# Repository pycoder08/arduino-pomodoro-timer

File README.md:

# Arduino Pomodoro Timer

A desktop focus timer I built around an Arduino Mega, a 16x2 LCD, three push buttons, a buzzer, and an RGB LED. It runs configurable focus/break cycles and signals each transition with color and sound.

## Status

The breadboard prototype works — I've run the timer through its focus and break cycles on it. The schematic and PCB layout are drawn in KiCad and included here. I'm currently soldering the circuit onto an Arduino protoshield.

I have not fabricated the custom PCB yet, so the layout is a work in progress rather than something I'd send to a fab house today. Routing and design-rule checks still need a pass.

## Features

- Three focus/break presets: 25/5, 15/5, and 50/10 minutes
- Start, pause, and resume, with the remaining time preserved across a pause
- Tap Reset to skip to the next phase; hold it for a second to cancel the session outright
- Preset selection with the mode button while idle, remembered in EEPROM across power cycles
- Count of sessions finished since power-on, shown on the idle screen
- Countdown on a 16x2 LCD
- Red RGB LED breathing during focus, solid green during breaks
- Multi-note buzzer melodies at session transitions

Button handling, the melodies, and the LED breathing are all non-blocking, so the countdown
stays accurate and the buttons stay responsive no matter what else is happening.

## Hardware

Arduino Mega 2560, 16x2 LCD, three push buttons, a passive buzzer, a common-cathode RGB LED,
resistors, breadboard, and jumper wire. LCD contrast comes from a fixed divider (roughly 8.5k to
5V and 1k to ground) rather than a trim potentiometer, so no pin is spent on it.

The sketch drives the RGB LED on pins 44–46. Those are PWM-capable on the Mega, which the
breathing effect needs, and they don't exist on a Uno — remap them if you build this on a smaller
board. I still need to document exact component models and resistor values.

### Pin assignments

| Function | Arduino pin |
| --- | --- |
| LCD RS | 12 |
| LCD enable | 11 |
| LCD D4–D7 | 5, 4, 3, 2 |
| Start / pause | 6 |
| Reset | 7 |
| Mode | 8 |
| Buzzer | 9 |
| RGB red | 44 |
| RGB blue | 45 |
| RGB green | 46 |

Buttons are wired active-low using `INPUT_PULLUP` and are debounced in software. This table covers
the software pin assignment only — check LCD contrast wiring, your RGB LED's common pin, and
current-limiting resistors against your own build.

## Running it

1. Open `timer.ino` in the Arduino IDE, letting it create the enclosing `timer` folder if prompted.
2. Make sure the `LiquidCrystal` library is installed. `EEPROM` ships with the IDE.
3. Select your board and port, confirming the pins above exist on it.
4. Compile and upload.

## KiCad files

`Timer.kicad_pro` is the main project, with `Timer.kicad_sch` for the schematic and `Timer.kicad_pcb` for the layout. `Arduino_MountingHole.pretty` holds the custom mounting-hole footprints the board references.

`focus_timer_schematic.kicad_sch` is an earlier sheet covering just the Arduino header connections, kept for reference.

## A note on the code

I wrote this project's firmware with AI assistance. The circuit design, breadboard build and testing, schematic capture, PCB layout, and protoshield assembly are my own work.

## To do

- Finish the protoshield soldering and retest every control
- Document component models and resistor values
- Run design-rule checks on the PCB before fabricating
- Test all three presets, pause/resume in both phases, tap and hold Reset, and the full
  focus-to-break transition
- Persist the session count across power cycles, or roll it over on a real clock rather than at
  power-on

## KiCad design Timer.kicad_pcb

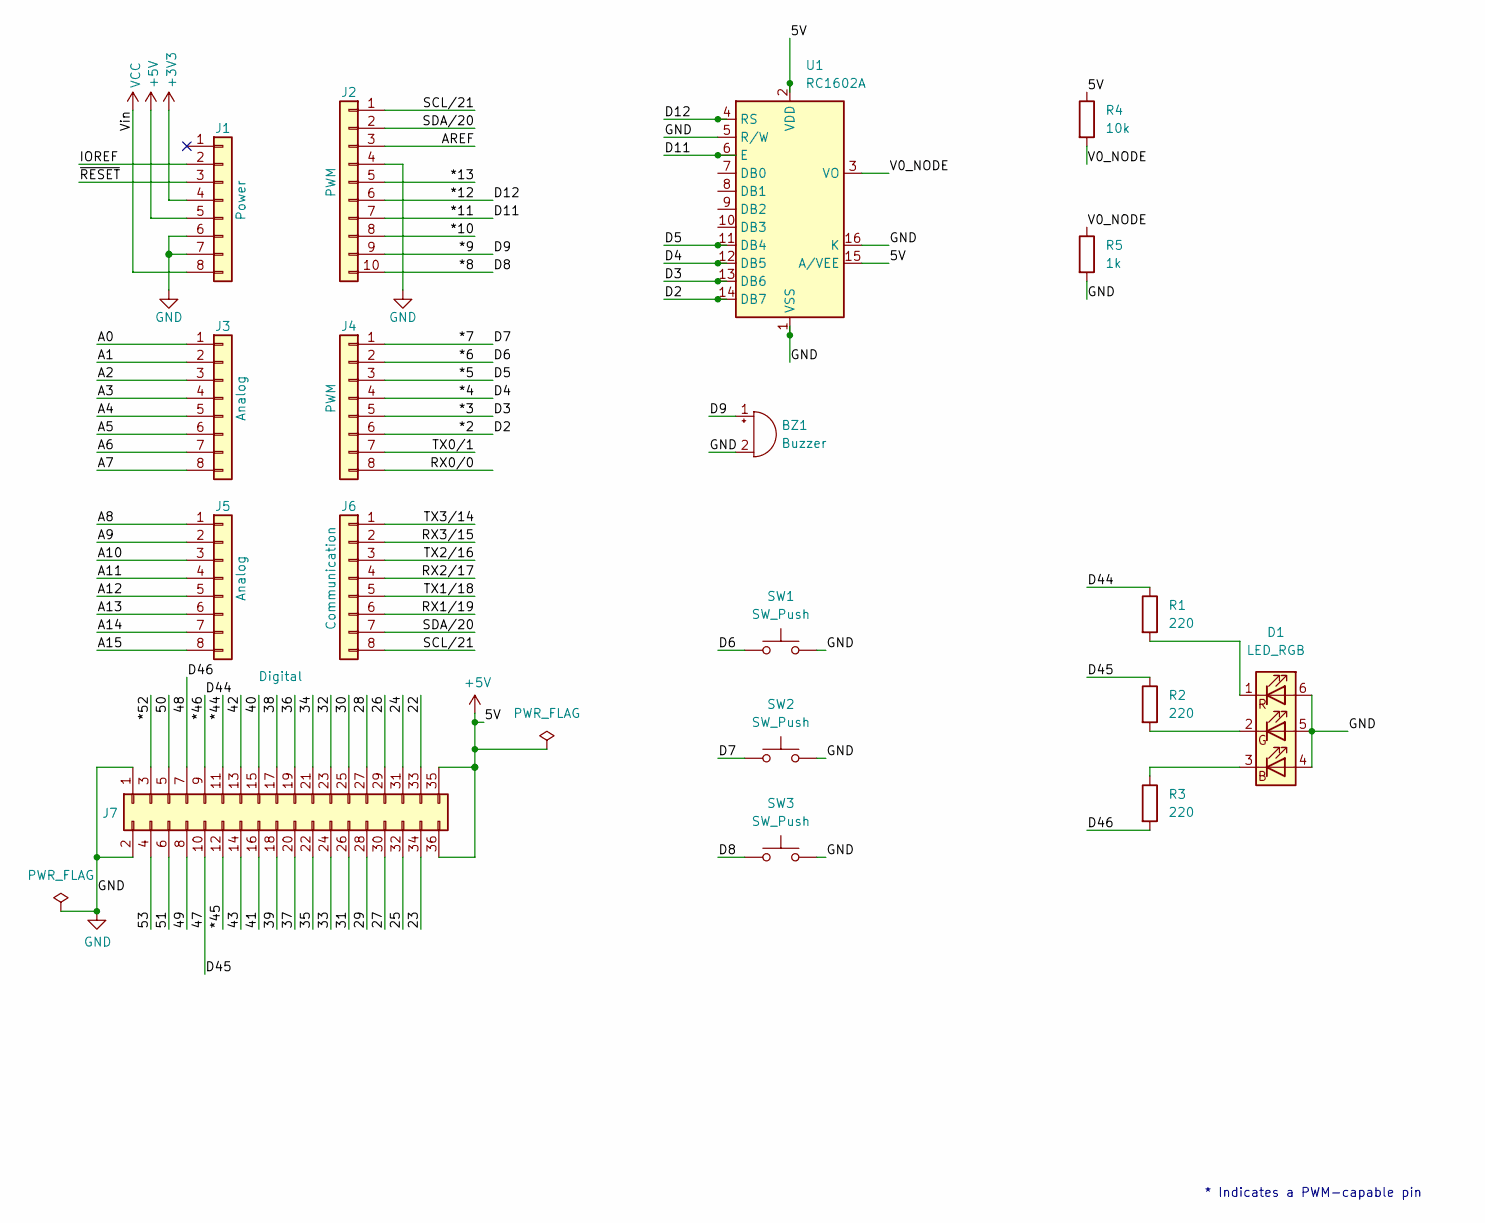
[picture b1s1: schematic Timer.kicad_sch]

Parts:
BZ1: Buzzer; MagneticBuzzer_ProSignal_ABT-410-RC
D1: LED_RGB; LED_RGB_5050-6
J1: Power; PinSocket_1x08_P2.54mm_Vertical
J2: PWM; PinSocket_1x10_P2.54mm_Vertical
J3, J5: Analog; PinSocket_1x08_P2.54mm_Vertical
J4: PWM; PinSocket_1x08_P2.54mm_Vertical
J6: Communication; PinSocket_1x08_P2.54mm_Vertical
J7: Digital; PinSocket_2x18_P2.54mm_Vertical
R1, R2, R3: 220; R_Axial_DIN0207_L6.3mm_D2.5mm_P10.16mm_Horizontal
R4: 10k; R_Axial_DIN0207_L6.3mm_D2.5mm_P10.16mm_Horizontal
R5: 1k; R_Axial_DIN0207_L6.3mm_D2.5mm_P10.16mm_Horizontal
SW1, SW2, SW3: SW_Push; SW_PUSH_6mm
U1: RC1602A

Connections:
+3V3: J1.4
+5V: J1.5, J7.35, J7.36, R4.1, U1.2 (VDD), U1.15 (A/VEE)
/22: J7.33
/23: J7.34
/24: J7.31
/25: J7.32
/26: J7.29
/27: J7.30
/28: J7.27
/29: J7.28
/30: J7.25
/31: J7.26
/32: J7.23
/33: J7.24
/34: J7.21
/35: J7.22
/36: J7.19
/37: J7.20
/38: J7.17
/39: J7.18
/40: J7.15
/41: J7.16
/42: J7.13
/43: J7.14
/47: J7.10, R2.1
/48: J7.7, R3.2
/49: J7.8
/50: J7.5
/51: J7.6
/53: J7.4
/*2: J4.6, U1.14 (DB7)
/*3: J4.5, U1.13 (DB6)
/*4: J4.4, U1.12 (DB5)
/*5: J4.3, U1.11 (DB4)
/*6: J4.2, SW1.1
/*7: J4.1, SW2.1
/*8: J2.10, SW3.1
/*9: BZ1.1 (+), J2.9
/*10: J2.8
/*11: J2.7, U1.6 (E)
/*12: J2.6, U1.4 (RS)
/*13: J2.5
/*44: J7.11
/*45: J7.12
/*46: J7.9, R1.1
/*52: J7.3
/A0: J3.1
/A1: J3.2
/A2: J3.3
/A3: J3.4
/A4: J3.5
/A5: J3.6
/A6: J3.7
/A7: J3.8
/A8: J5.1
/A9: J5.2
/A10: J5.3
/A11: J5.4
/A12: J5.5
/A13: J5.6
/A14: J5.7
/A15: J5.8
/AREF: J2.3
/IOREF: J1.2
/RX0/0: J4.8
/RX1/19: J6.6
/RX2/17: J6.4
/RX3/15: J6.2
/SCL/21: J2.1, J6.8
/SDA/20: J2.2, J6.7
/TX0/1: J4.7
/TX1/18: J6.5
/TX2/16: J6.3
/TX3/14: J6.1
/V0_NODE: R4.2, R5.1, U1.3 (VO)
/~RESET: J1.3
GND: BZ1.2 (-), D1.4 (BA), D1.5 (GA), D1.6 (RA), J1.6, J1.7, J2.4, J7.1, J7.2, R5.2, SW1.2, SW2.2, SW3.2, U1.1 (VSS), U1.5 (R/W), U1.16 (K)
unnamed: D1.3 (BK), R3.1
unnamed: D1.2 (GK), R2.2
unnamed: D1.1 (RK), R1.2
VCC: J1.8

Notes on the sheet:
* Indicates a PWM-capable pin

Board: 2 copper layers, 24 parts (0 on the bottom side), 21 nets, no tracks yet.

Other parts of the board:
MH1, MH2, MH3, MH4, MH5, MH6: MountingHole_3.2mm
